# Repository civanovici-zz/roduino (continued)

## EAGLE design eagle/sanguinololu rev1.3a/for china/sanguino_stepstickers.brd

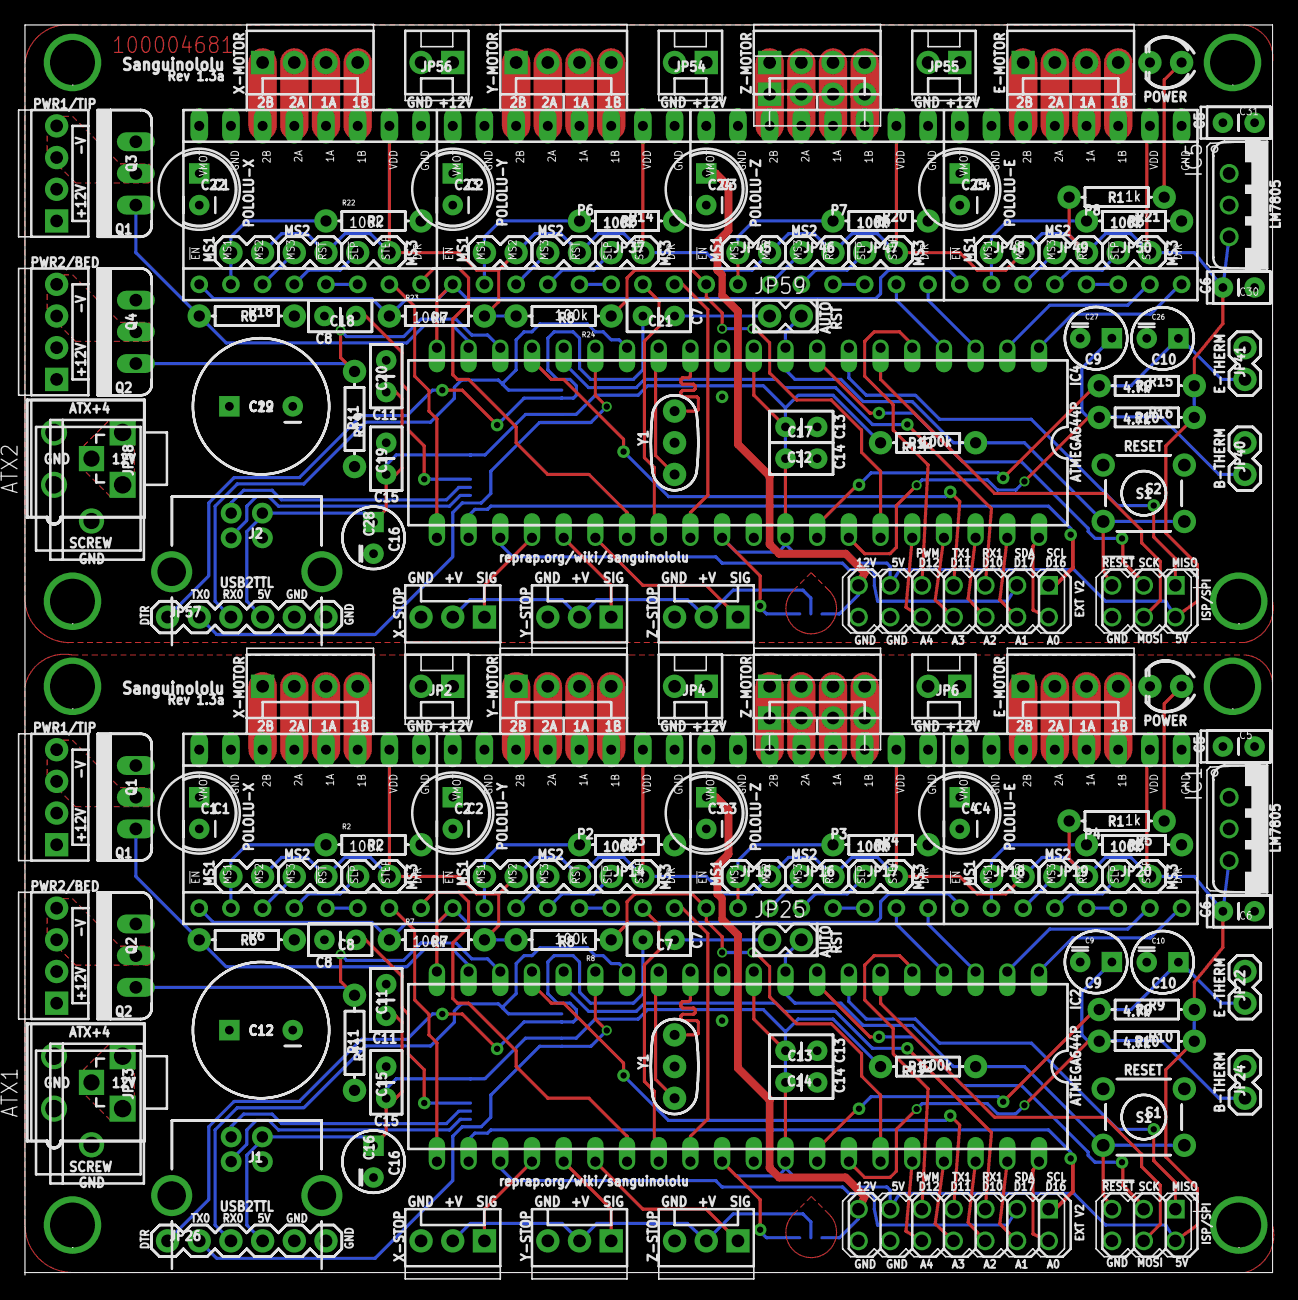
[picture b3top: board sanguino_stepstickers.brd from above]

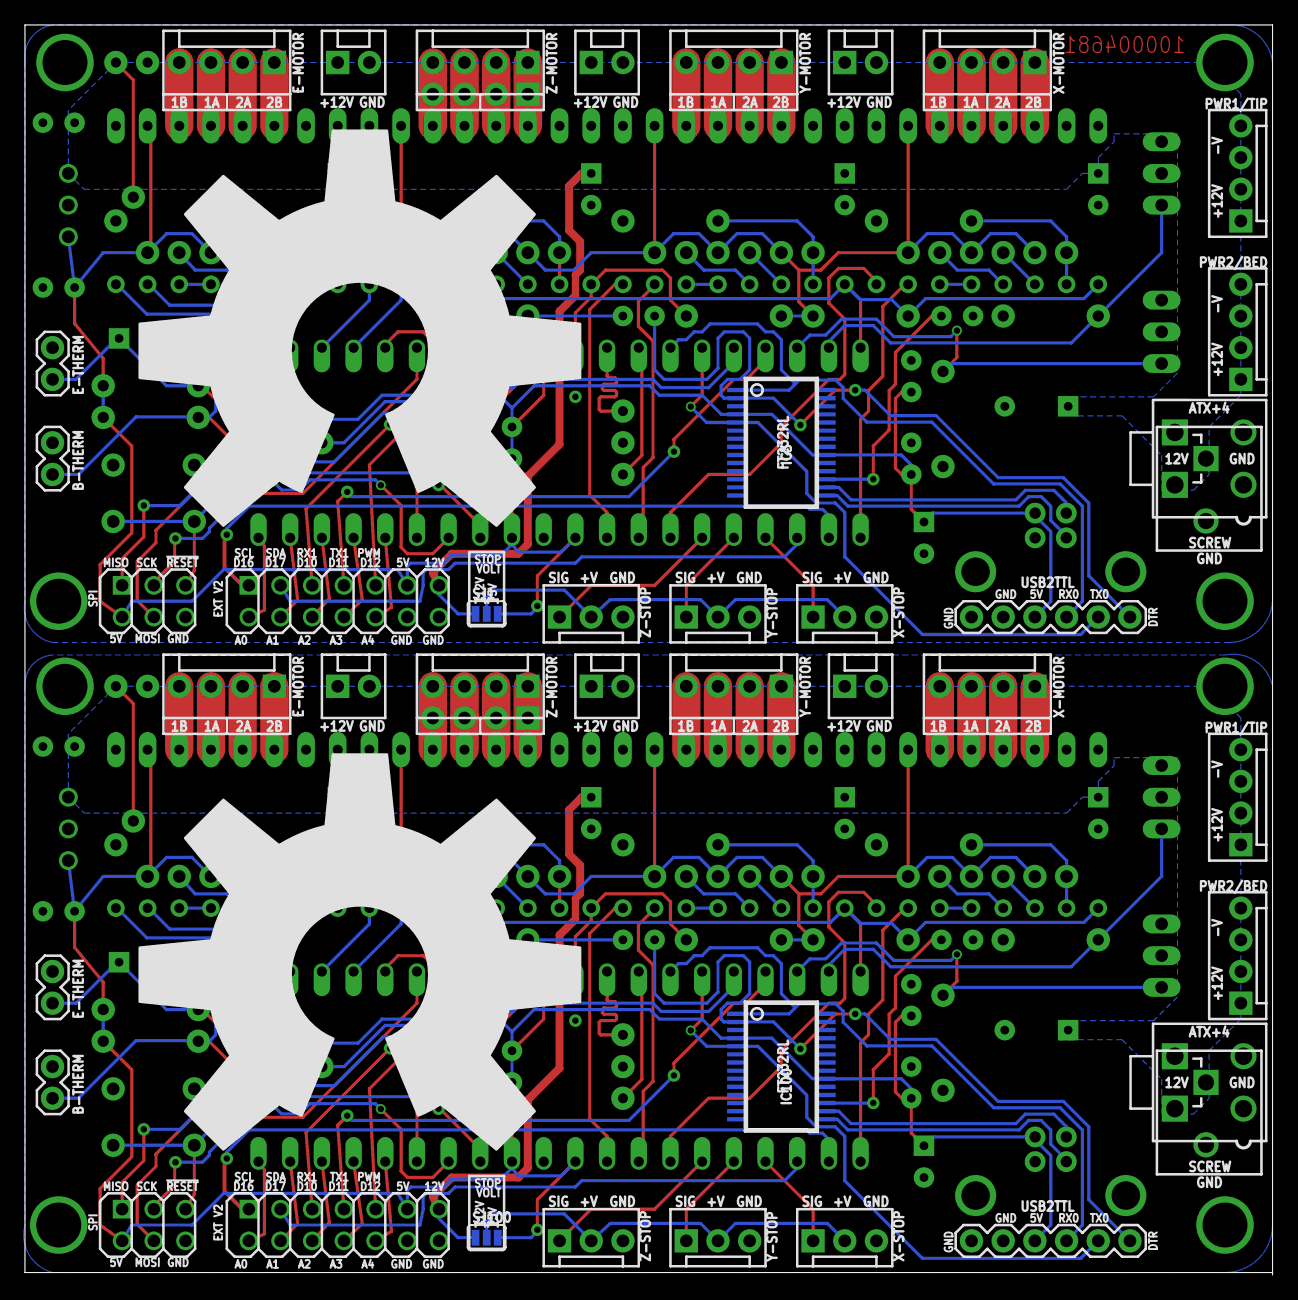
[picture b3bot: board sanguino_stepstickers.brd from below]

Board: 2 copper layers, 100.0 x 100.0 mm, 154 parts (4 on the bottom side), 158 nets.

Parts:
ATX1, ATX2: ATX-4VERTICAL; MINIFITJR-4-VERTICAL
C1, C2, C3, C4, C22, C23, C24, C25: 100uf; CPOL-RADIAL-100UF-25V
C5, C31: 0.33uF; CAP-PTH-SMALL2
C6, C7, C8, C11, C13, C14, C15, C17, C18, C19, C20, C21, C30, C32: 0.1uF; CAP-PTH-SMALL2
C9, C10, C26, C27: 10uF; CPOL-RADIAL-10UF-25V
C12, C29: 1000uF; CPOL-RADIAL-1000UF-25V
C16, C28: 4.7uF; CPOL-RADIAL-10UF-25V
IC1, IC5: LM7805; 78XXL-CUSTOM
IC2, IC4: ATMEGA644-20PU; DIL40
IC3, IC100: FT232RL; SSOP28DB
J1, J2: USB; USB-B-PTH
JP1, JP31: MOT-X; MOLEX-1X4
JP2, JP4, JP6, JP54, JP55, JP56: 12VPWR; MOLEX-1X2
JP3, JP32: MOT-Y; MOLEX-1X4
JP5, JP30, JP33, JP60: MOT-Z; MOLEX-1X4
JP7, JP34: MOT-E; MOLEX-1X4
JP8, JP38: HOTEND; MOLEX-1X4
JP9, JP51: X-MS1; 1X02
JP10, JP52: X-MS2; 1X02
JP11, JP53: X-MS3; 1X02
JP12, JP35: Y-MS1; 1X02
JP13, JP36: Y-MS2; 1X02
JP14, JP37: Y-MS3; 1X02
JP15, JP45: Z-MS1; 1X02
JP16, JP46: Z-MS2; 1X02
JP17, JP47: Z-MS3; 1X02
JP18, JP48: E-MS1; 1X02
JP19, JP49: E-MS2; 1X02
JP20, JP50: E-MS3; 1X02
JP21, JP39: HOTBED; MOLEX-1X4
JP22, JP41: E-THERM; 1X02
JP23, JP58: SCREW; SCREWTERMINAL-5MM-2
JP24, JP40: B-THERM; 1X02
JP25, JP59: AUTO RESET; 1X02
JP26, JP57: USB2TTL; 1X06
JP27, JP42: X-STOP; MOLEX-1X3
JP28, JP43: Y-STOP; MOLEX-1X3
JP29, JP44: Z-STOP; MOLEX-1X3
LED1, LED2: POWER; LED3MM
P1, P5: POLOLU-X; POLOLU-ALLEGRO-PTH
P2, P6: POLOLU-Y; POLOLU-ALLEGRO-PTH
P3, P7: POLOLU-Z; POLOLU-ALLEGRO-PTH
P4, P8: POLOLU-E; POLOLU-ALLEGRO-PTH
Q1, Q2, Q3, Q4: RFP30N06LE; TO220V
R1, R17: 1k; AXIAL-0.3
R2, R3, R4, R5, R7, R8, R12, R13, R14, R20, R21, R22, R23, R24: 100k; AXIAL-0.3
R6, R11, R18, R19: 10k; AXIAL-0.3
R9, R10, R15, R16: 4.7k; AXIAL-0.3
S1, S2: RESET; TACTILE-PTH
SJ1, SJ100: 5v/12v; SJ_3
U$1, U$24: IO_HEADERS_SCREW; IO_HEADER-PLATEDSCREW
U$2, U$3, U$4, U$17, U$37, U$38: PLATED-SCREW; PLATEDSCREW
Y1, Y2: 16MHz 22pF; RESONATOR-PTH

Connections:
3V1: C18.1, IC3.17
3V3: C8.1, IC100.17
5V: C6.1, C11.1, C13.2, C14.1, C15.1, C16.1, IC1.OUT, IC2.10, IC2.30, IC2.32, IC100.4, IC100.20, J1.VBUS, JP9.2, JP10.2, JP11.2, JP12.2, JP13.2, JP14.2, JP15.2, JP16.2, JP17.2, JP18.2, JP19.2, JP20.2, JP26.4, P1.VDD, P2.VDD, P3.VDD, P4.VDD, R1.P$2, R7.P$2, R8.P$2, R9.P$2, R10.P$2, R12.P$2, SJ100.3, U$24.5V, U$24.5V1
5V1: C17.2, C19.1, C20.1, C28.1, C30.1, C32.1, IC3.4, IC3.20, IC4.10, IC4.30, IC4.32, IC5.OUT, J2.VBUS, JP35.2, JP36.2, JP37.2, JP45.2, JP46.2, JP47.2, JP48.2, JP49.2, JP50.2, JP51.2, JP52.2, JP53.2, JP57.4, P5.VDD, P6.VDD, P7.VDD, P8.VDD, R13.P$2, R15.P$2, R16.P$2, R17.P$2, R23.P$2, R24.P$2, SJ1.3, U$1.5V, U$1.5V1
12V: ATX1.3, ATX1.4, C1.1, C2.1, C3.1, C4.1, C5.1, C12.1, IC1.IN, JP2.1, JP4.1, JP6.1, JP8.1, JP8.2, JP21.1, JP21.2, JP23.1, P1.VMOT, P2.VMOT, P3.VMOT, P4.VMOT, SJ100.1, U$24.12V
12V1: ATX2.3, ATX2.4, C22.1, C23.1, C24.1, C25.1, C29.1, C31.1, IC5.IN, JP38.1, JP38.2, JP39.1, JP39.2, JP54.1, JP55.1, JP56.1, JP58.1, P5.VMOT, P6.VMOT, P7.VMOT, P8.VMOT, SJ1.1, U$1.12V
!FTDI-RESET: C7.1, JP25.1
!FTDI-RESET1: C21.1, JP59.1
!HOTBED: IC2.18, Q2.1, R11.P$1
!HOTBED1: IC4.18, Q4.1, R19.P$1
!HOTEND: IC2.19, Q1.1, R6.P$1
!HOTEND1: IC4.19, Q3.1, R18.P$1
!RESET: IC2.9, JP25.2, R12.P$1, S1.3, S1.4, U$24.RST
!RESET1: IC4.9, JP59.2, R13.P$1, S2.3, S2.4, U$1.RST
!STEP-ENABLE: IC2.20, P1.!EN, P2.!EN, P4.!EN, R7.P$1
!STEP-ENABLE1: IC4.20, P5.!EN, P6.!EN, P8.!EN, R23.P$1
!STEP-ENABLE-Z: IC2.35, P3.!EN, R8.P$1
!STEP-ENABLE-Z1: IC4.35, P7.!EN, R24.P$1
#DTR: C7.2, IC100.2, JP26.1
#DTR1: C21.2, IC3.2, JP57.1
A0: IC2.40, U$24.A0
A1: IC2.39, U$24.A1
A2: IC2.38, U$24.A2
A3: IC2.37, U$24.A3
A4: IC2.36, U$24.A4
A5: IC4.40, U$1.A0
A6: IC4.39, U$1.A1
A7: IC4.38, U$1.A2
A8: IC4.37, U$1.A3
A9: IC4.36, U$1.A4
AIFO: IC2.14, IC100.1, JP26.3
AIFO1: IC3.1, IC4.14, JP57.3
AOFI: IC2.15, IC100.5, JP26.2
AOFI1: IC3.5, IC4.15, JP57.2
B-THERM: C9.1, IC2.34, JP24.1, R10.P$1
B-THERM1: C27.1, IC4.34, JP40.1, R16.P$1
E-DIR: IC2.1, P4.DIR
E-DIR1: IC4.1, P8.DIR
E-MOT-1A: JP7.3, P4.1A
E-MOT-1A1: JP34.3, P8.1A
E-MOT-1B: JP7.4, P4.1B
E-MOT-1B1: JP34.4, P8.1B
E-MOT-2A: JP7.2, P4.2A
E-MOT-2A1: JP34.2, P8.2A
E-MOT-2B: JP7.1, P4.2B
E-MOT-2B1: JP34.1, P8.2B
E-MS1: JP18.1, P4.MS1, R5.P$1
E-MS2: JP19.1, P4.MS2
E-MS3: JP20.1, P4.MS3
E-MS4: JP48.1, P8.MS1, R21.P$1
E-MS5: JP49.1, P8.MS2
E-MS6: JP50.1, P8.MS3
E-RESETSLEEP: P4.!RST, P4.!SLP
E-RESETSLEEP1: P8.!RST, P8.!SLP
E-STEP: IC2.2, P4.STEP
E-STEP1: IC4.2, P8.STEP
E-THERM: C10.1, IC2.33, JP22.1, R9.P$1
E-THERM1: C26.1, IC4.33, JP41.1, R15.P$1
ENDSTOP+V: JP27.2, JP28.2, JP29.2, SJ100.2
ENDSTOP+V1: JP42.2, JP43.2, JP44.2, SJ1.2
GND: ATX1.1, ATX1.2, C1.2, C2.2, C3.2, C4.2, C5.2, C6.2, C8.2, C9.2, C10.2, C11.2, C12.2, C13.1, C14.2, C15.2, C16.2, IC1.GND, IC2.11, IC2.31, IC100.7, IC100.18, IC100.21, IC100.25, IC100.26, J1.GND, J1.P$1, J1.P$2, JP2.2, JP4.2, JP6.2, JP22.2, JP23.2, JP24.2, JP26.5, JP26.6, JP27.3, JP28.3, JP29.3, LED1.K, P1.GNDMOT, P1.GNDVDD, P2.GNDMOT, P2.GNDVDD, P3.GNDMOT, P3.GNDVDD, P4.GNDMOT, P4.GNDVDD, Q1.3, Q2.3, R2.P$2, R3.P$2, R4.P$2, R5.P$2, R6.P$2, R11.P$2, S1.1, S1.2, U$17.GND, U$24.GND, U$24.GND1, U$24.GND2, U$24.GNDSCREW, U$37.GND, U$38.GND, Y1.2
GND1: ATX2.1, ATX2.2, C17.1, C18.2, C19.2, C20.2, C22.2, C23.2, C24.2, C25.2, C26.2, C27.2, C28.2, C29.2, C30.2, C31.2, C32.2, IC3.7, IC3.18, IC3.21, IC3.25, IC3.26, IC4.11, IC4.31, IC5.GND, J2.GND, J2.P$1, J2.P$2, JP40.2, JP41.2, JP42.3, JP43.3, JP44.3, JP54.2, JP55.2, JP56.2, JP57.5, JP57.6, JP58.2, LED2.K, P5.GNDMOT, P5.GNDVDD, P6.GNDMOT, P6.GNDVDD, P7.GNDMOT, P7.GNDVDD, P8.GNDMOT, P8.GNDVDD, Q3.3, Q4.3, R14.P$2, R18.P$2, R19.P$2, R20.P$2, R21.P$2, R22.P$2, S2.1, S2.2, U$1.GND, U$1.GND1, U$1.GND2, U$1.GNDSCREW, U$2.GND, U$3.GND, U$4.GND, Y2.2
HOTBED-GND: JP21.3, JP21.4, Q2.2
HOTBED-GND1: JP39.3, JP39.4, Q4.2
HOTEND-GND: JP8.3, JP8.4, Q1.2
HOTEND-GND1: JP38.3, JP38.4, Q3.2
LED1: LED1.A, R1.P$1
LED2: LED2.A, R17.P$1
PB4-PWM: IC2.5, U$24.PWM
PB4-PWM1: IC4.5, U$1.PWM
PB5-MOSI: IC2.6, U$24.MOSI
PB5-MOSI1: IC4.6, U$1.MOSI
PB6-MISO: IC2.7, U$24.MISO
PB6-MISO1: IC4.7, U$1.MISO
PB7-SCK: IC2.8, U$24.SCK
PB7-SCK1: IC4.8, U$1.SCK
PC0-SCL: IC2.22, U$24.SCL
PC0-SCL1: IC4.22, U$1.SCL
PC1-SDA: IC2.23, U$24.SDA
PC1-SDA1: IC4.23, U$1.SDA
PD2-RX1: IC2.16, U$24.RX1
PD2-RX2: IC4.16, U$1.RX1
PD3-TX1: IC2.17, U$24.TX1
PD3-TX2: IC4.17, U$1.TX1
USBDM: IC100.16, J1.D-
USBDM1: IC3.16, J2.D-
USBDP: IC100.15, J1.D+
USBDP1: IC3.15, J2.D+
X-DIR: IC2.27, P1.DIR
X-DIR1: IC4.27, P5.DIR
X-MOT-1A: JP1.3, P1.1A
X-MOT-1A1: JP31.3, P5.1A
X-MOT-1B: JP1.4, P1.1B
X-MOT-1B1: JP31.4, P5.1B
X-MOT-2A: JP1.2, P1.2A
X-MOT-2A1: JP31.2, P5.2A
X-MOT-2B: JP1.1, P1.2B
X-MOT-2B1: JP31.1, P5.2B
X-MS1: JP9.1, P1.MS1, R2.P$1
X-MS2: JP10.1, P1.MS2
X-MS3: JP11.1, P1.MS3
X-MS4: JP52.1, P5.MS2
X-MS5: JP53.1, P5.MS3
X-MS6: JP51.1, P5.MS1, R22.P$1
X-RESETSLEEP: P1.!RST, P1.!SLP
X-RESETSLEEP1: P5.!RST, P5.!SLP
X-STEP: IC2.21, P1.STEP
X-STEP1: IC4.21, P5.STEP
X-STOP: IC2.24, JP27.1
X-STOP1: IC4.24, JP42.1
XTAL1: IC2.13, Y1.3
XTAL2: IC2.12, Y1.1
XTAL3: IC4.12, Y2.1
XTAL4: IC4.13, Y2.3
Y-DIR: IC2.29, P2.DIR
Y-DIR1: IC4.29, P6.DIR
Y-MOT-1A: JP3.3, P2.1A
Y-MOT-1A1: JP32.3, P6.1A
Y-MOT-1B: JP3.4, P2.1B
Y-MOT-1B1: JP32.4, P6.1B
Y-MOT-2A: JP3.2, P2.2A
Y-MOT-2A1: JP32.2, P6.2A
Y-MOT-2B: JP3.1, P2.2B
Y-MOT-2B1: JP32.1, P6.2B
Y-MS1: JP12.1, P2.MS1, R3.P$1
Y-MS2: JP13.1, P2.MS2
Y-MS3: JP14.1, P2.MS3
Y-MS4: JP35.1, P6.MS1, R14.P$1
Y-MS5: JP36.1, P6.MS2
Y-MS6: JP37.1, P6.MS3
Y-RESETSLEEP: P2.!RST, P2.!SLP
Y-RESETSLEEP1: P6.!RST, P6.!SLP
Y-STEP: IC2.28, P2.STEP
Y-STEP1: IC4.28, P6.STEP
Y-STOP: IC2.25, JP28.1
Y-STOP1: IC4.25, JP43.1
Z-DIR: IC2.3, P3.DIR
Z-DIR1: IC4.3, P7.DIR
Z-MOT-1A: JP5.3, JP30.3, P3.1A
Z-MOT-1A1: JP33.3, JP60.3, P7.1A
Z-MOT-1B: JP5.4, JP30.4, P3.1B
Z-MOT-1B1: JP33.4, JP60.4, P7.1B
Z-MOT-2A: JP5.2, JP30.2, P3.2A
Z-MOT-2A1: JP33.2, JP60.2, P7.2A
Z-MOT-2B: JP5.1, JP30.1, P3.2B
Z-MOT-2B1: JP33.1, JP60.1, P7.2B
Z-MS1: JP15.1, P3.MS1, R4.P$1
Z-MS2: JP16.1, P3.MS2
Z-MS3: JP17.1, P3.MS3
Z-MS4: JP46.1, P7.MS2
Z-MS5: JP47.1, P7.MS3
Z-MS6: JP45.1, P7.MS1, R20.P$1
Z-RESETSLEEP: P3.!RST, P3.!SLP
Z-RESETSLEEP1: P7.!RST, P7.!SLP
Z-STEP: IC2.4, P3.STEP
Z-STEP1: IC4.4, P7.STEP
Z-STOP: IC2.26, JP29.1
Z-STOP1: IC4.26, JP44.1
